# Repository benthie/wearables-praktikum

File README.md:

<br>
<i>     a project by Marlene Fiedler, Lorenz Miething and Benjamin Thiemann</i><br>
<br>
In the context of the lab course "Wearable Computing Systems", which started at the end of Oct 2016, we were asked to build our own wearable device. Our idea since then was to build a blink detection system that recognizes the user's lack of blinking when sitting in front of the computer. With a distance sensor that is monitoring the eye and a custom-built software the user of our wearable will be stimulated to blink by blurring the computer screen.

#Documentation

Now - at the end of the project - we proudly present our results. All the single bits and pieces of our project have been documented in order to deliver high reusability for anybody who wants to work on the project after the end of the semester the lab took place. This repository is mainly devided into the two sub parts hardware and software. The hardware itself consists of two different PCBs and the fixation parts to fix the PCBs to different kinds of glasses, as well as 3D printed glasses for users who usually do not wear any. All documenting files should enable you to rebuild the hardware such that you have a working system, which will be accepted by the software parts and then run without difficulty.<br>
<br>
The developed software has been published under the open source MIT License and is running as it is. It consists of two parts, namely an RFduino sketch and a Mac OS X Cocoa application. The sketch for the RFduino contains the blink detection algorithm and is able to communicate with the Cocoa app via Bluetooth Low Energy. For detailed information about the blink detection algorithm please see [here](#eye-blink-detection-algorithm). The Cocoa app's source code has both copious commenting and a [Doxygen documentation](https://benthie.github.io/wearables-praktikum/). The application's graphical user interface will be explained [below](#eyedrops-cocoa-application) and is additionally explained in a short [video](https://youtu.be/3qRnkdi4qJQ).

##Table of contents
- [Requirements](#requirements)
- [How to use](#how-to-use)
- [Hardware](#hardware)
  - [VCNL4020](#vcnl4020)
  - [RFduino](#rfduino)
  - [3D-printed parts](#3d-printed-parts)
- [Eye blink detection algorithm](#eye-blink-detection-algorithm)
- [eyeDrops Cocoa Application](#eyedrops-cocoa-application)
  - [Blur mode](#blur-mode)
  - [Bluetooth connection](#establishing-bluetooth-le-connection)
  - [User profile manager](#user-profile-manager)
  - [Preferences](#preferences)
  - [Calibration](#calibration)
  - [Ready to use](#ready-to-use)
  - [Executable File](#executable-file)
  - [Doxygen documentation](https://benthie.github.io/wearables-praktikum/)
- [Live Demo](#live-demo)
- [Credits](#credits)
- [License](#license)

###Requirements
- Arduino IDE ([Arduino software](https://www.arduino.cc/en/main/software)) 
- RFduino Package ([Link to the Git](https://github.com/RFduino/RFduino/blob/master/README.md))
- Mac OS X (sorry for that crucial restriction!)
- Bluetooth Low Energy (BLE - also called Bluetooth 4.0) capable Mac
- RFduino USB Shield ([RFD22121](http://www.rfduino.com/product/rfd22121-usb-shield-for-rfduino/index.html) or [RFD22124](http://www.rfduino.com/product/rfd22124-pcb-usb-shield-for-rfduino/index.html))
- CorePlot Framework ([Installation Guide](https://github.com/core-plot/core-plot/wiki/Using-Core-Plot-in-an-Application))

###How to use

So how to use our wearable? Simply grab the 3d-printed clips and the fitting slider, mount the electronics together with a battery pack on it, which then altogether forms the so called "<b>wearable</b>" and make sure that your Mac fullfills the above requirements. Plug the RFduino USB shield into your Mac and upload our [RFduino sketch](software/RFduino) to the wearable. After completing this step the last thing to do is to download the [Xcode project](software/cocoa-app), follow the [CorePlot library installation guide](https://github.com/core-plot/core-plot/wiki/Using-Core-Plot-in-an-Application) and start the eyeDrops application and have fun exploring.<br>
<br>
<i>Note:</i> If you want to use the compiled and built application (.app file) please follow the steps described in section [Executable File](#executable-file).

#Hardware

Our Hardware consits mainly of three parts: The sensor that is detecting the blinks, the microcontroller RFduino and our 3D-printed parts, used to hold the sensor and microcontroller in place.

##VCNL4020

The sensor used in our wearable is the VCNL4020 (http://www.vishay.com/docs/83476/vcnl4020.pdf). It is a proximity and ambient light sensor with a built-in infrared emitter and photo diode. The data obtained from the sensor vary, depending on how much light is reflected back to the sensor. Due to its high 16-bit-resolution and the operating range from 1 to 200 mm, it is possible to determine the difference of distance when pointing at an open or a closed eyelid. The data of the VCNL4020 can be transferred via an I²C Interface. Furthermore, interrupts can be sent. 

<p align="center">

<br>Figure 1: Sensor VCNL4020.
</p>

A custom PCB was designed for the VCNL4020. The goal was to get a board that can be attached to a clip, mounted in the front of spectacles, worn by the user. In order to not disturb the user while working, the PCB should be as small as possible. The first design featured pull-up resistors for the data, clock and interrupt signals, decoupling capacitors and five header pins for power supply, the I²C interface and the interrupt signal. 

<p align="center">

<br>Figure 2: First PCB design for VCNL4020.
</p>

However, the first PCB design had to be revised due to its size, by moving the pull-up resistors to the second PCB and using small pads instead of the header pins. The revised PCB features a size of only 11 mm times 12 mm. The schematics and layouts of both versions  can be found [here](https://github.com/benthie/wearables-praktikum/tree/master/hardware/eagle).

The revised PCB was milled, using a Cirqoid CNC mill (http://cirqoid.com/). Both the milled PCB without components and the populated PCB can be seen here:

<p align="center">

<br>Figure 3: milled PCB for VCNL4020.
</p>

<p align="center">

<br>Figure 4: populated PCB for VCNL4020.
</p>

A ribbon cable was attached to the pads, so that the PCB for the VCNL can be connected to the RFduino PCB, which will be described in the following chapter.

##RFduino

The microcontroller used in our project is an RFduino (http://www.rfduino.com/) which features a bluetooth low energy (BLE) compatible radio transceiver. It can be programmed using the Arduino IDE.

<p align="center">

<br>Figure 5: RFduino
</p>

A custom PCB was made for the RFduino, featuring a 3.3 V voltage regulator, decoupling capacitors, a reset button, the mentioned pull-up resistors for the VCNL4020, header pins to connect to the ribbon cable leading to the VCNL4020 PCB, header pins for programming the RFduino and a screw terminal for the input voltage. The populated PCB can be seen here:

<p align="center">

<br>Figure 6: PCB for RFduino 
</p>

The schematic and layout of the PCB can be found [here](https://github.com/benthie/wearables-praktikum/tree/master/hardware/eagle).

#Eye blink detection algorithm

The blink detection algorithm can be divided in a filtering and a processing stage. The logarithmically scaled incoming raw data of the sensor are converted into distances of arbitrary unit. Any offset is removed by computing the differences between the samples and an equally weighted moving average filter with a window size of 16 (experimentally determined) is applied to the derivative of the data. With that, the filtering stage is completed and the actual detection algorithm begins, which is applied to the last 200 samples.<br>
Instead of going through all samples within that window for every new sample, the characteristic values are kept in real time as the samples come in.<br>
In order to understand the algorithm more easily let’s first have a look at the pattern that has to be detected. Since the different eye blinks vary in duration and peak height as shown in figure 7, the algorithm has to accomodate for this dynamic behaviour. 
<p align="center">

<br>Figure 7: Accumulated eye blinks with varying durations from single person
</p>
Therefore, a simple pattern correlation would not perform very well. Instead, the algorithm looks for a certain dynamic pattern in the preprocessed data. It performs edge detection and zero crossing detection by comparing the current value with the previous one. The values are split into four areas: above positive threshold, between positive threshold and zero, between zero and negative threshold and below negative threshold. With this in mind six different crossings can be detected creating the following algorithm to detect the actual eye blink as shown in figure 8.
<p align="center">

<br>Figure 8: Step by step blink detection
</p>
1. Zero has to be crossed from a positive to a negative value. This means that the measured distance is decreasing and the eye lid is closing. Zero was just cross for point 1.
2. The negative threshold is crossed downwards. This means that the measured distance decreases less significantly and the eye lid stops closing.
3. The negative threshold is crossed upwards. At this point the minimum value and its index between the two negative threshold crossings is determined from the sample buffer. If the sample number between the initial zero crossing and the determined minimum value is within a certain range and the minimim value is above a certain value. With that the first neces- sary condition is met and the blink level indicating the progress of the current eye blink to be detected is increased by one.
4. Zero is crossed upwards. This does not affect the algorithm and can happen multiple times with alter- nating downward zero crossings at this stage. The number of zero crossings is recorded for further anal- ysis at a later stage of the algorithm and refers to the duration the eye is closed during an eye blink.
5. The positive threshold is crossed upwards. This means that the eye lid is beginning to open again.
6. The positive threshold is crossed downwards. At this point the maximum value and its index between the two positive threshold crossings is determined. If the sample number between the last minimum value and the maximum value is within a certain range, the number of zero crossings does not exceed a certain limit, the maximum value itself does not exceed a certain value either, and the blink level has a value of 1 indicating a previes eye closing event, the blink level is increased again by one. This means the eye is stopping to open and therefore almost open again. It is now assumed, that an actual eye blink was detected for real time application.<br>If any of the above conditions is not met, the blink level is reset to zero.
7. Zero is crossed downwards. If the overall duration of the eye blink is within a certain range the blink detection is complete, the blink level is reset to zero and an eye blink is reported. This means that the eye is fully open again or at least the eye lid movement cannot be detected by the sensor anymore for the remaining eye opening procedure.

The actual threshold crossing detection is extended with a hysteresis procedure. In order to cross a threshold upwards the threshold plus a hysteresis value has to be crossed.
In order to cross it downwards, the threshold minus a hysteresis value has to be crossed. This ensures, that a small fluctuation in the data caused by noise does not mess up the steps of the algorithm. The hysteresis is shown as a gray area in figure 8.<br>
Testing this algorithm on multiple persons showed that it does not necessarily work out of the box for everybody but certain paramaters such as the thresholds, hysteresis and sample distances between the steps have to be adjusted. As shown in figure 7 the durations and peak values for only a single person differs from eye blink to eye blink. Looking at the data for different persons this varies even more.

##3D-printed parts

The 3D-printed parts include a clip and slider for the VCNL4020 PCB, a clip for the RFduino and spectacles for users who do not usually wear them. These parts were designed using the 3D CAD software Solidworks (http://www.solidworks.de/) and printed using the 3D-printer Makerbot Replicator 2X (https://store.makerbot.com/printers/replicator2x/). The used filament consists of ABS.

<p align="center">

<br>Figure 9: 3D-Printer Makerbot Replicator 2X
</p>

Since our product shall be usable with the users own spectacles, both clips were designed in three different sizes, so that they can be attached to temple arms of different widths. The clip for the VCNL4020 was made as small as possible and printed with transparent filament, in order to reduce the impact in the visual field of the user.

<p align="center">

<br>Figure 10: Clip for VCNL4020 PCB
</p>

Due to different anatomies of different users, like smaller or bigger eyes, eyeballs located further in- or outside the head, etc., it should be possible to adjust the position of the VCNL4020 PCB. Therefore, the PCB is not directly attached to the clip, but instead attached to a slider, which is itself slided into the clip.

<p align="center">

<br>Figure 11: Slider for VCNL4020 PCB
</p>

The slider was designed with different inclinations, so that the angle between the temple arms and the PCB can be adjusted. There are also sliders that lower the position of the PCB with respect to the height of the temple arms. These exchangable sliders allow adjustment to different anatomies.

<p align="center">

<br>Figure 12: lower Slider for VCNL4020 PCB
</p>

In order to make adjustments easier, we designed further clips containing magnets. With these, it was possible to attach magnet-containing 3D-printed adapter that were stuck to the PCB. These adapters were also printed with different inclinations, so that, depending on the users anatomy, the sensor would always be well adjusted. However, very thin magnets were not strong enough to hold the adapter in place and thicker magnets were too thick, so that the PCB was encountered disturbing for the user.
Another approach was a 3D-printed ball joint, which could not be used neither, due to the low printing quality for very small round objects. <br>
<br>

In order to attach the RFduino PCB to the users spectacles, there is another clip. This clip is used without a slider. Instead the PCB is directly attached to the clip, held by two tappets. There is a cavity in the clip, so that the reset button of the PCB can be pressed easily.

<p align="center">

<br>Figure 13: Clip for RFduino PCB
</p>

The 3D-printed spectacles with the attached clips can be seen in the following graphic:

<p align="center">

<br>Figure 14: Spectacles with clips 
</p>

The SLDPRT-files as well as the 3D-printing-files for the described parts can be found [here](https://github.com/benthie/wearables-praktikum/tree/master/hardware/3dprinting).

#eyeDrops Cocoa application

The eyeDrops application is designed to offer a highly comfortable interface between the user and the wearable. The main task of the entire system is to detect a lack of blinking and then react correspondingly. Our implemented reaction to such a lack of blinking is a progressive blurring of the screen in order to enforce an eye blink. A blurred screen can be cleared by a simple blink, which was apparently long overdue. And since the app only needs to control the screen, it was designed as a pure menubar application, that is having no active window but just an icon in the menu bar.<br>
<br>
We chose Mac OS X as the target operating system after a long period of attemps (with a lot of effort) to deliver a platform independent software for our wearable. In the end it was a sum of facts that influenced our decision. The main problem, to begin with, was to build a software that is able to blur the complete screen. Here, Java was the first programming language we tried, but we could not achieve a working version. To do so, one would have to enter a very low level graphics programming since Java cannot make use of a window compositing manager. With Cocoa and Objective-C on the other hand, we could deliver a working blurring of the screen by simply using Quartz Compositor of OS X. In the following process we tried to stick to Java for the main program, but then there was no working BLE stack for Java around that would work on all desired platforms (Windows, Mac, Linux) and thus there was no need to stick to Java anymore. Since two third of the developers were using a Mac and we already had a working software for blurring the screen, it stood to reason that we write the complete software just for Mac. And that is what we did after all.<br>
<br>
To get the eyeDrops application running, download the source code from the [software folder](/software/cocoa-app) and launch `eyeDrops.xcodeproj` with Xcode. Make sure that you properly include the CorePlot framework as described [here](https://github.com/core-plot/core-plot/wiki/Using-Core-Plot-in-an-Application). The project is now ready to be built. The following documentation explains how to use the application you should be able to see now.

##Blur mode

<p align="center">

<br>Figure 15: Application in off state.
</p>

As you can see in figure 15, there is no active window but only a menubar icon which pops down a usual menu when you click on it. In the above image the icon is gray and not white, telling the user that blur mode is turned off.

<p align="center">

<br>Figure 16: Application in on state.
</p>

In figure 16, however, the icon is white and thus signalizing that blur mode is activated. To switch bewteen those two states simply <b>ctrl-click</b> on the menubar item. If blur mode is actived and in case that a device is connected, the screen would be blurred if the user did not blink in adjustable time interval. See the [settings](#preferences) section for more information about the allowed time interval without an eye blink.

##Establishing Bluetooth (LE) Connection<a name="establishing-bluetooth-le-connection" />

In order to establish a bluetooth connection with the wearable, which is the next necessary and logical step when setting up the system, the first thing to do is scanning for bluetooth nearby. This can be either done via the menuitem <i>Scan for devices</i> or automatically by the app. The latter way needs a setting in the <i>General</i> tab in the [Preferences Window](#preferences).<br>
<br>
After a successful scan all the available devices are listed in the submenu <i>Available Devices</i>. Connecting to the device can again be done either via selecting the corresponding menuitem or automatically by the app. The second way needs a setting in the <i>General</i> tab in the [Preferences Window](#preferences).<br>

<p align="center">

<br>Figure 17: List of available devices.
</p>

A connected device is represented with a check mark next to its name. Another click on that same menuitem would then cancel the connection with the device. Selecting another device which is currently not the connected one would simply switch the connection to that device.<br>
<br>
In case that a connection was successfully established, the wearable now needs a user profile to work with. This user profile contains the paramerters used by the blink detection algorithm. Without a valid user the wearable will be idle.

##User profiles / profile manager<a name="user-profile-manager" />

In order to obtain a valid user profile either load an XML file containing one or more valid profiles or use the systems [calibration](#calibration) procedure to create a new profile.

<p align="center">

<br>Figure 18: Preferences - User profile manager.
</p>

The default directory the app is working in is `/Users/<CurrentUser>/eyeDrops` = `~/eyeDrops`, where `<CurrentUser>` is the name of the currently logged in user. This directory is created during the app's launching process and will of course not be overwritten if it already exists. You can put your XML file in this directory and restart the app, which will lead to an automatic reading of the profiles contained in XML file, or you click <i>Browse</i> in the <i>Profiles</i> tab in the Preferences Window (see figure 18) and manually select your XML file there. After setting the new path, the profiles will be automatically read from the file and displayed in the TableView in the profile manager. Selecting a profile from that table will display the user profile's content in the TextView next to the table. It is also possible to delete a profile by clicking <i>Delete profile</i> or to create a new profile by clicking <i>Create new profile</i>, which will then open up the [calibration window](#calibration).

##Preferences

The system wide settings can be changed in the <i>General</i> tab in the Preferences Window (see figure 19). When starting the eyeDrops app for the first time, this settings will be initialized with values we used during the development phase. When properly closing the app, all made changes will be stored in `settings.txt` in the default directory and reloaded at the next launching process. That way your settings do not get lost.

<p align="center">

<br>Figure 19: Preferences - General settings.
</p>

###Blurring settings
- <b>Maximal Blur Radius:</b> determines how strong your screen gets finally blurred.
- <b>Blur Step:</b> determines the step increase while blurring (the smaller the value, the smoother the blurring).
- <b>Blur Speed:</b> determines the time delay between two steps (the smaller the value, the longer the blurring up to the maximal radius takes).
- <b>Allowed Time Without Blinking:</b> the time interval in which at least one blink has to occur.

###Bluetooth settings
- <b>Automatically scan:</b> determines whether the app automatically scans for devices.
- <b>Automatically connect:</b> determines whether the app automatically connects to the last known device.

###Battery Level
- This LevelIndicator shows the battery level of the wearable. The indication here is not really proportional to the battery voltage but to the voltage after the voltage regulator in the PCB. <!--For more information about this see the [report TODO](/docs/report.pdf).-->

##Calibration

As explained above, calibration is essential for having a properly working blink detection algorithm. Since every eye is unique, differing shapes, sizes and positions in the skull are what the sensor is facing. And due to those inequalities the measured distances to the eye vary from one user to the other. The implemented calibration procedure let's the user define his or her individual calibration parameters, which are then uploaded to the wearable as well as stored in a profile on the computer. More information about the calibration and the different parameters used to detect a blink is elaborately described [above](#eye-blink-detection-algorithm).

<p align="center">

<br>Figure 20: Calibration window - On start-up.
</p>

Figure 20 shows the calibration window directly after start-up. Both eyeDrops app and wearable are now in calibration mode  where the RFduino can be triggered to continuously send data packages containing sensor raw data and information about whether a blink was detected or not until a stop message arrives.

<p align="center">

<br>Figure 21: Calibration animation (two successive steps).
</p>

A custom-built animation (see figure 21) is used to guide the user through the data acquisition phase of the calibration. This phase takes nine seconds and should contain four blinks (represented by the larger circles). It can be run testwise without receiving any data, just to get to know the procedure by clicking the button <i>Run Test</i>.<br>
<br>
The completion of the data acquisition will be announced by an pop-up alert with instructions for the next steps. Afterwards the data will be plotted in the two designated graphs.

<p align="center">

<br>Figure 22: Calibration window - After receiving and plotting the sensor and blink data.
</p>

A completed data acquisition phase can be seen in figure 22. The preset values on the right side of the calibration window turned out to make sense for most of test users and can be adopted for new profiles without being worried about bad performance. The only two values that are mandatory to be set by the user are the threshold values. These can be obtained by simply clicking on the sensor data graph (top). A red and a blue line will appear for negative resprectively positive threshold. Place the lines such that any noise lies between the threshold values. A good guiding value is to set the thresholds to half of it's max value. After setting the threshold values the user can either do another calibration with the newly gained values and check if the algorithm now detects (more) blinks or directly save the profile with the option to directly use the new profile.<br>

###Ready to use

Now that a valid profile has been created and uploaded to the wearable, the system is ready to use. Enable the [blur mode](#blur-mode) and enjoy the experience with the system.

###Using the Cocoa executable (.app file)<a name="executable-file" />

If you do not want to always launch the application out of Xcode, you can use an executable .app file. After running the app out of Xcode, an .app file has been automatically created there. In your project navigator in Xcode you can find it in the `Products` folder. Right-click on `eyeDrops.app` and select `Show in Finder`. The opened folder contains the app as well as two frameworks. Those frameworks must be copied into `/System/Library/Frameworks` to make the `eyeDrops.app` launchable.

##Live Demo

[Link to youtube video](https://www.youtube.com/embed/3qRnkdi4qJQ)

##Credits

<b>The Noun Project - Source for the used items:</b>
- <i>Rohit M S:</i> Creator of the main icon
- <i>Nicolas Morand:</i> Creator of the profiles icon
- <i>Guilhem:</i> Creator of the battery icon
- <i>Viktor Vorobyev:</i> Creator of the bluetooth icon

##License

This project has been published under the MIT License.

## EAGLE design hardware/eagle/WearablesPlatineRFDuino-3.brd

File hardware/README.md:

Hardware folder, consisting layout, datasheets etc.

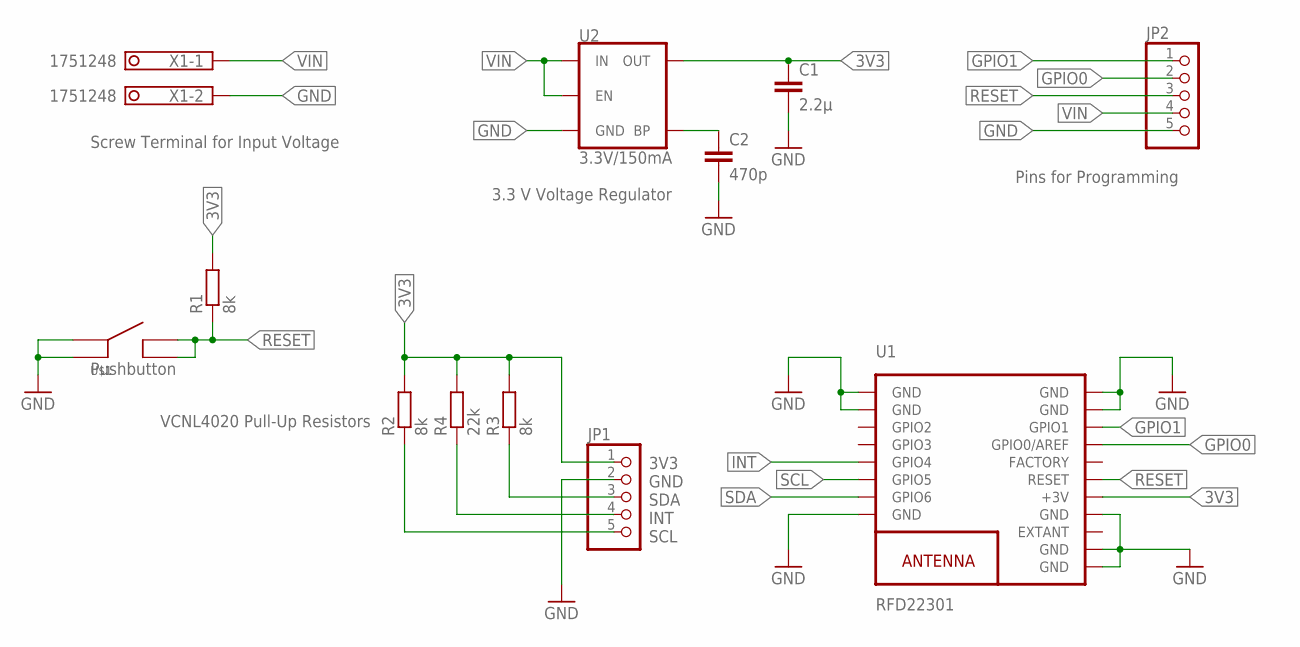
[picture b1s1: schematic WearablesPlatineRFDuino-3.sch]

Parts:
C1: 2.2µ; C0603
C2: 470p; C0603
JP1, JP2: PINHD-1X5; 1X05
R1, R2, R3: 8k; R0603
R4: 22k; R0603
U1: RFD22301
U2: 3.3V/150mA; SOT23-5
U$1: TACTILE_SWITCH; EVQ-PUK02K
X1: 1751248

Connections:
3V3: C1.1, JP1.1, R1.2, R2.2, R3.2, R4.2, U1.13 (+3V), U2.5 (OUT)
GND: C1.2, C2.2, JP1.2, JP2.5, U1.1 (GND), U1.2 (GND), U1.8 (GND), U1.9 (GND), U1.10 (GND), U1.12 (GND), U1.18 (GND), U1.19 (GND), U2.2 (GND), U$1.1 (A), U$1.3 (A), X1.2
GPIO0: JP2.2, U1.16 (GPIO0/AREF)
GPIO1: JP2.1, U1.17 (GPIO1)
INT: JP1.4, R4.1, U1.5 (GPIO4)
unnamed: C2.1, U2.4 (BP)
RESET: JP2.3, R1.1, U1.14 (RESET), U$1.2 (B), U$1.4 (B)
SCL: JP1.5, R2.1, U1.6 (GPIO5)
SDA: JP1.3, R3.1, U1.7 (GPIO6)
VIN: JP2.4, U2.1 (IN), U2.3 (EN), X1.1

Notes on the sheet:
Screw Terminal for Input Voltage
3V3 GND SDA INT SCL
VCNL4020 Pull-Up Resistors
Pins for Programming
3.3 V Voltage Regulator
Pushbutton

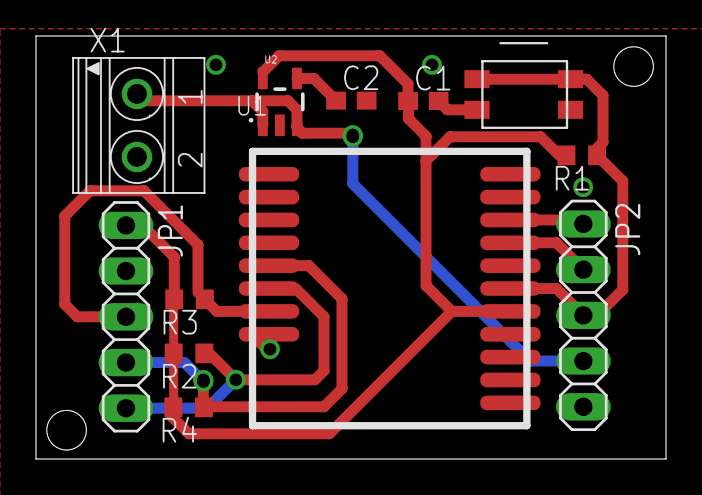
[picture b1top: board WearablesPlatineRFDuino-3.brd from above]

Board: 2 copper layers, 35.0 x 23.5 mm, 12 parts (0 on the bottom side), 10 nets.

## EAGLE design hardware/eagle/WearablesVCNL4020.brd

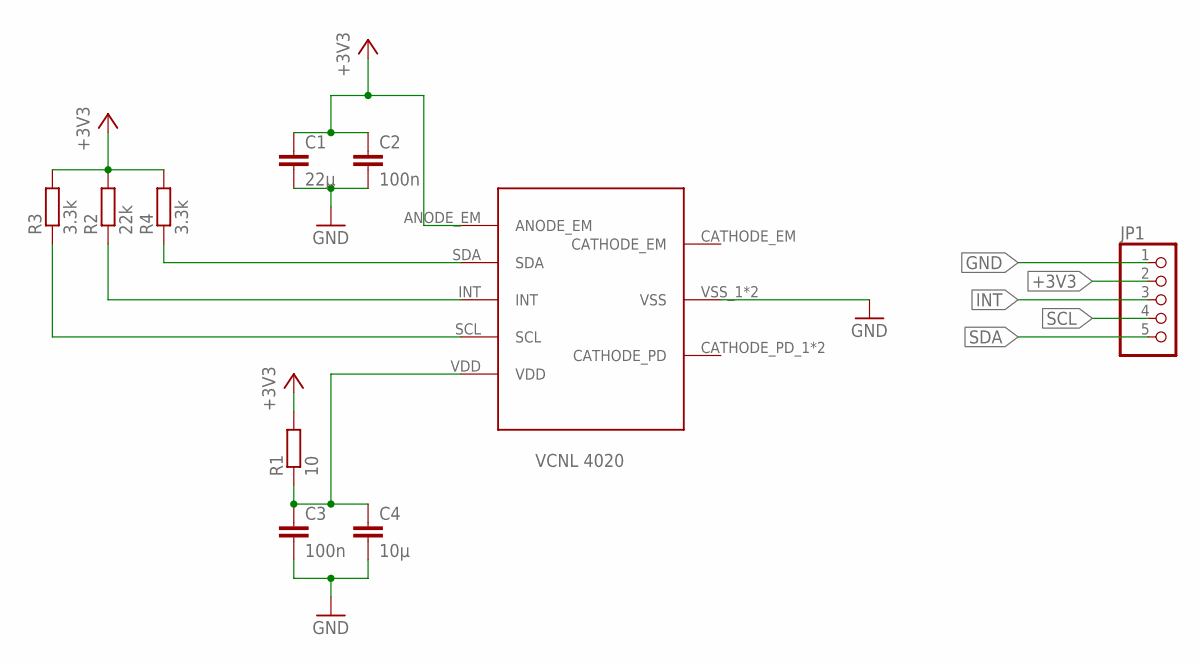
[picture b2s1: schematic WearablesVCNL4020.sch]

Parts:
C1: 22µ; C0805
C2, C3: 100n; C0805
C4: 10µ; C0805
JP1: PINHD-1X5/90; 1X05/90
R1: 10; R0805
R2: 22k; R0805
R3, R4: 3.3k; R0805
U$1: VCNL4020

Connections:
+3V3: C1.1, C2.1, JP1.2, R1.2, R2.2, R3.2, R4.2, U$1.ANODE_EM
GND: C1.2, C2.2, C3.2, C4.2, JP1.1, U$1.VSS_1 (VSS), U$1.VSS_2 (VSS)
INT: JP1.3, R2.1, U$1.INT
SCL: JP1.4, R3.1, U$1.SCL
SDA: JP1.5, R4.1, U$1.SDA
VDD: C3.1, C4.1, R1.1, U$1.VDD

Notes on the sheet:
VCNL 4020

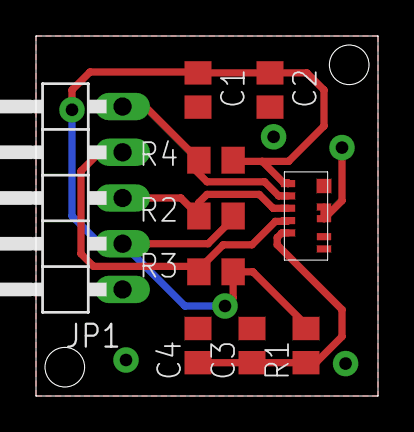
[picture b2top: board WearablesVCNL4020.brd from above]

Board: 2 copper layers, 19.0 x 20.0 mm, 10 parts (0 on the bottom side), 6 nets.

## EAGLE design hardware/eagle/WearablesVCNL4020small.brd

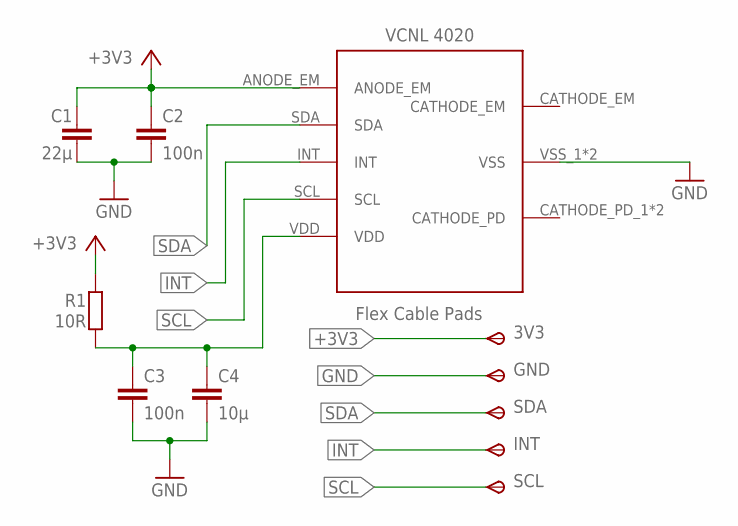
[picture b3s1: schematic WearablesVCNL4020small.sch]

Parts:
3V3: TPSTP08R; TP08R
C1: 22µ; C0603
C2, C3: 100n; C0603
C4: 10µ; C0603
GND: TPSTP08R; TP08R
INT: TPSTP08R; TP08R
R1: 10R; R0603
SCL: TPSTP08R; TP08R
SDA: TPSTP08R; TP08R
U$1: VCNL4020

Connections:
+3V3: 3V3.TP, C1.1, C2.1, R1.2, U$1.ANODE_EM
GND: C1.2, C2.2, C3.2, C4.2, GND.TP, U$1.VSS_1 (VSS), U$1.VSS_2 (VSS)
INT: INT.TP, U$1.INT
SCL: SCL.TP, U$1.SCL
SDA: SDA.TP, U$1.SDA
VDD: C3.1, C4.1, R1.1, U$1.VDD

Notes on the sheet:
VCNL 4020
Flex Cable Pads

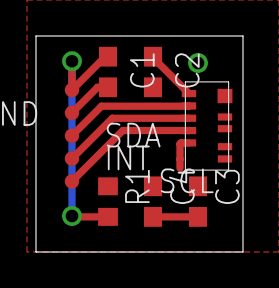
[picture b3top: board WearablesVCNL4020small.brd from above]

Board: 2 copper layers, 11.5 x 12.0 mm, 11 parts (0 on the bottom side), 6 nets.

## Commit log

2016-12-18 Adjusted folder structure
2016-12-18 added documents folder
2016-12-18 Added initial group presentation
2016-12-18 Added gantt chart for midterm presentation
2016-12-18 added image self built poc for presentation
2016-12-18 Remove schematics from tracking
2016-12-19 Updated version of the presentation
2016-12-20 Added Marlenes Part and final version of Presentation
2017-01-17 wip Midterm presenstation
2017-02-13 Create docs
2017-02-27 Added gitignore and deleted docs/readme.md
2017-02-27 updated schematics and board files.
2017-02-27 added documented Arduino code.
2017-02-27 Deleted redundent files
2017-02-27 change folder names
2017-02-27 added file for git
2017-02-27 finally XCode project added
2017-02-27 Doxygen documentation added
2017-02-27 Doxygen documentation main page changed
2017-02-27 Remove index.html
2017-02-27 Doxygen documentation main page changed, typo removed
2017-02-28 .nojekyll added in order to allow underscore in html file names
2017-02-28 Doxygen documentation updated
2017-02-28 Doxygen documentation deleted
2017-02-28 Doxygen documentation updated - jeykyll turned off
2017-03-03 wip add algorithm description
2017-03-03 added images for blink detection algorithm
2017-03-03 wip added details for blink detection algorithm
2017-03-03 updated and completed description of algorithm
2017-03-03 fix formatting
2017-03-03 updated references
2017-03-03 fixed references
2017-03-03 updated youtube link
2017-03-03 added video to documentation
2017-03-03 updated video link
2017-03-03 Readme.md deleted.
2017-03-03 software/RFDuino updated.

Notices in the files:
README.md:
License:
This project has been published under the MIT License.
parts and their libraries:
SparkFun-IC-Power: Licensing: Creative Commons ShareAlike 4.0 International - https://creativecommons.org/licenses/by-sa/4.0
